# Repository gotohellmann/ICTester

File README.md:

# ICTester

IC Tester for the classic CMOS and TLL ICs with Touch Display

**Beware 5V ICs only!**

GPL v3 License - Open Hard- and Software

Code by  **Frank Hellmann**, 2019
http://www.gotohellmann.com/

based on **Akshay Bawejas** code
http://www.akshaybaweja.com/
https://github.com/akshaybaweja/Smart-IC-Tester

If you like it please leave a ⭐!

For hardware requirements and libraries used see below

### Versions:

**Version 2.6**
----------------------------------------------
- update: updated chipdb.txt with 150+ new ICs
          and checked in new test vectors
- new:    version string for chipdb.txt
- new:    Z tag in chipdb.txt for high-Z check
          needs PCB rework for 1M pull-downs,
          checks not implemented in Version 2.6
- new:    NOVECTORS tag for ICs without tests
          this will only display the IC in manual
- bugfix: Auto: sometimes displays wrong IC pinout    
- update: new CLK code for multiple clockpins
          (thanks, @Hans Hübner)
- new:    Auto: flip result pages back and fore

**Version 2.5**
----------------------------------------------
- new:    added LED support to code
- bugfix: pin order corrected for 20pin ICs
- update: updated chipdb.txt with new ICs
- overall "refactoring" of code ;)

 ### Platform & Hardware needed:
 
- This project needs the [Arduino IDE 1.8.10+](https://www.arduino.cc/en/software)
- a **Arduino Mega 2560** Module
- an **ILI9341** 240x320 Pixel RGB TFT LCD Touch Display Shield
- a 4GB Micro-SD Card that fits the Display Shield 
- the IC Tester PCB with:
   - a 20pin ZIF Socket
   - single row pinheaders (1x6pin, 1x8pin, and two 2x18pin)
   - optional Red/Green-LED (Common Cathode) plus two 220Ohm resistors
   - optional White LED plus one 220Ohm resistors and some heatshrink tubing

### Populating the PCB

- Place the PCB with the soldermask upwards and the ZIF socket left hand side
- First solder the ZIF socket with the lever downwards, as the silkscreen shows
- Optional Good/Fail LED:
    - Solder the Red/Green LED with the Red LED towards the left side
    - Solder in the two 220Ohm resistors R2 and R3
- Optional Worklight LED:
    - Solder in the 220Ohm resistor R1 
    - Keep the long legs of the LED and use some heatshrink to avoid shorts
    - Solder the white LED in and position it
- Solder in the pinheaders
- Plug TFT and PCB into the Arduino Mega 2560

### Setting Up and Programming

- Format the SDCard as FAT/FAT32 Filesystem
- Copy the database (data/chipdb.txt) into the root folder of the SDCard (chipdb.txt)
- Plug the SDCard into the TFT shield and connect the Arduino Mega to the computer  
- Start the Arduino IDE
- Check you have the following librarys installed (Tools -> Library Manager):
  - **MCUFRIEND_kbv**  (try the **Adafruit_ILI9341** if the display doesn't work)
  - **Adafruit GFX Library**  (included the Bus Library as well)
  - **Adafruit Touchscreen**
- Install the _patched_ SD library from this repository (Sketch -> Library -> .ZIP )
  - **SD_patched** (download from above, includes Arduino Mega Software SPI fix)
- Open the **IC_Tester_v2.6.ino** 
- Select the proper **Arduino Mega 2560** under Tools -> Board -> Arduino AVR Boards
- Select the correct COM port for upload
- Compile and Upload the sketch

### Usage

  **Beware: This Tester is for testing 5V ICs only!**

- Start the IC Tester and marvel at the startup screen 😏 
- Touch to enter main screen
- Make sure the ZIF socket lever is up
- Insert IC as shown on the screen with the notch facing up and pull the lever down

**There are two modes of operation:**
- **Auto** tries to detect what kind of IC is inserted. This is helpful if you have no
  markings on the IC. To use it you'll have to adjust the number of pins of the IC
  with the **Pins** Button and then hit **Auto**. The IC Tester will match it against
  the known ICs and give you the results. You can press the touch screen to go through
  each found match.

- **Manual** will check an inserted IC against the tests stored in the database.
  Hit **Manual** and insert the plain IC number without the family code here
  (an 74HC06 should be entered as *7406*) and hit **OK**. This will run the test and
  display the results. You can savely change the IC and retest again, if you have a
  few of the same type to test.
  
  The manual mode can also be used to get the pinout of an IC. Just leave the socket empty.

### Troubleshooting

- Display doesn't work:
  Most of the TFT Touch Display shields work with parallel inputs, that's the reason to use
  the MCUFRIEND_kbv library. If your display does not work, using the original Adafruit_ILI9341
  library could help.

- SD Card Error:
  The chipdb.txt couldn't be read. Either the file is corrupt (copy it again),  the card formated
  with the wrong filesystem (format it with FAT), the card to big (best 4GB or below) or an older SPI 
  library interfers with the the TFT Touch Display shield. If this is the case, install the SD_patched Library
  from this repository above.

### Help needed!

- I do not have all possible TTL 74** or CMOS 4*** ICs here for testing. So if you'll find one, that shows up
  as "*** not found" consider sending it in or add it to the chipdb.txt and test it. The format is pretty
  straight forward.

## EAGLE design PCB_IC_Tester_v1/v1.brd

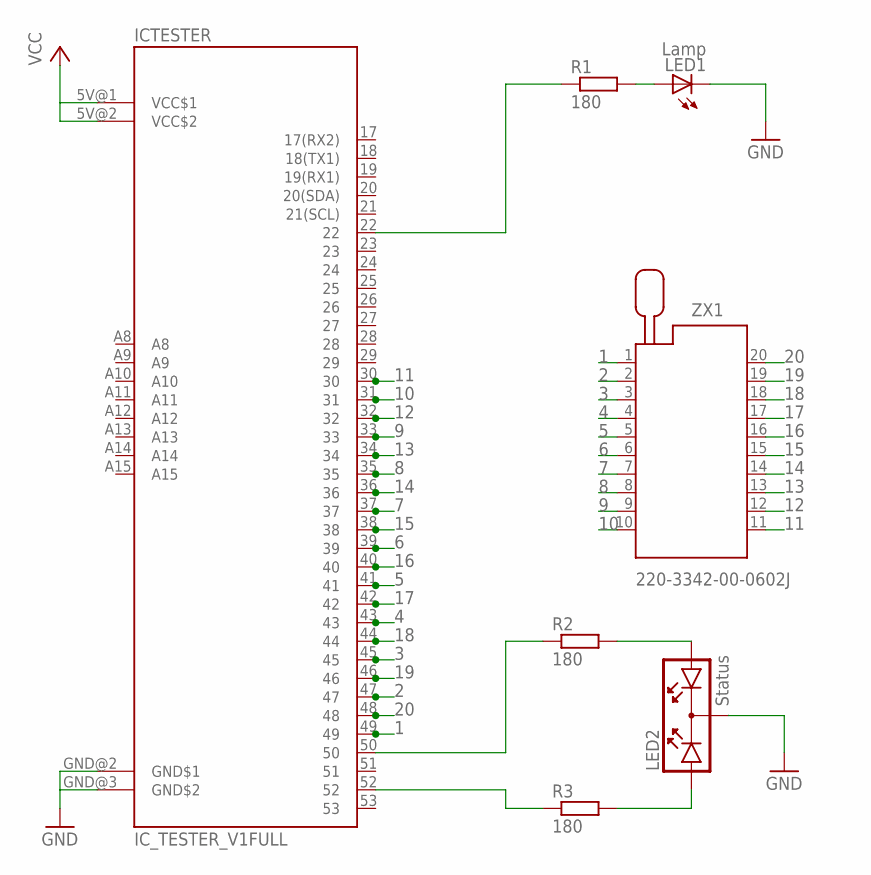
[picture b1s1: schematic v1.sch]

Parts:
ICTESTER: IC_TESTER_V1FULL; SPARKFUN-BOARDS_ARDUINO_MEGA
LED1: Lamp; LED3MM
LED2: Status; DUOLED
R1, R2, R3: 180; 0204V
ZX1: 220-3342-00-0602J

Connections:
1: ICTESTER.49, ZX1.1
2: ICTESTER.47, ZX1.2
3: ICTESTER.45, ZX1.3
4: ICTESTER.43, ZX1.4
5: ICTESTER.41, ZX1.5
6: ICTESTER.39, ZX1.6
7: ICTESTER.37, ZX1.7
8: ICTESTER.35, ZX1.8
9: ICTESTER.33, ZX1.9
10: ICTESTER.31, ZX1.10
11: ICTESTER.30, ZX1.11
12: ICTESTER.32, ZX1.12
13: ICTESTER.34, ZX1.13
14: ICTESTER.36, ZX1.14
15: ICTESTER.38, ZX1.15
16: ICTESTER.40, ZX1.16
17: ICTESTER.42, ZX1.17
18: ICTESTER.44, ZX1.18
19: ICTESTER.46, ZX1.19
20: ICTESTER.48, ZX1.20
GND: ICTESTER.GND@2 (GND$1), ICTESTER.GND@3 (GND$2), LED1.K (C), LED2.K
unnamed: LED1.A, R1.2
unnamed: LED2.A2, R2.2
unnamed: LED2.A1, R3.2
unnamed: ICTESTER.50, R2.1
unnamed: ICTESTER.52, R3.1
unnamed: ICTESTER.22, R1.1
VCC: ICTESTER.5V@1 (VCC$1), ICTESTER.5V@2 (VCC$2)

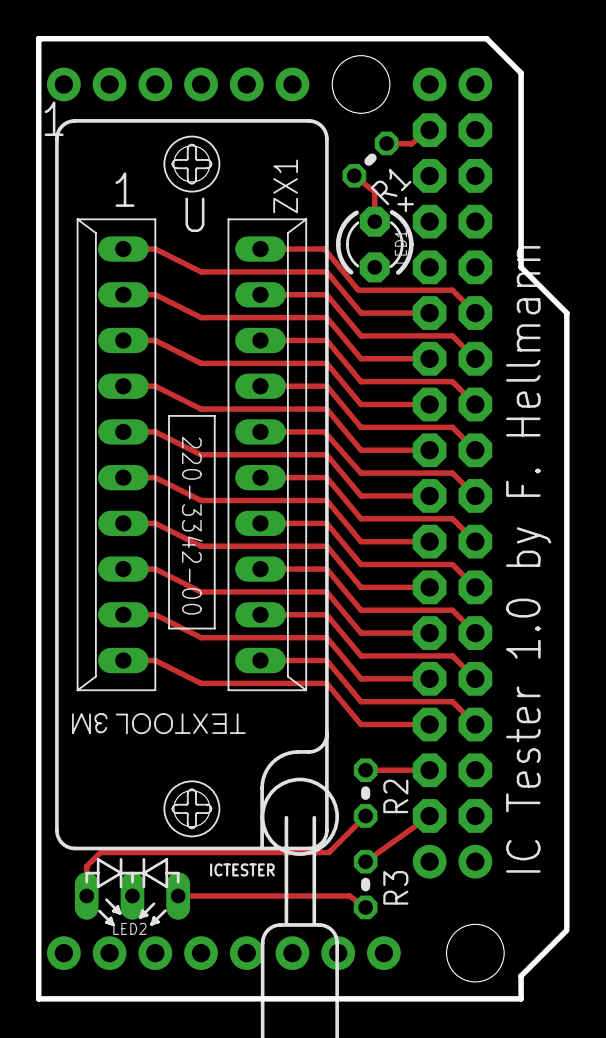
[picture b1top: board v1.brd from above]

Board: 2 copper layers, 29.3 x 53.3 mm, 7 parts (0 on the bottom side), 28 nets.

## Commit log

2021-01-27 Initial commit
    Arduino codebase and database commited
2021-01-27 Initial Commit
    Eagle Project and Gerbers
2021-01-31 Update IC_Tester_v2.5.ino
    include SD_patched.h with Arduino Mega 2560 Software SPI patches
2021-01-31 Patched SD.h Library
    This library contains a patched SD.h library to access SD Cards with Software SPI on an Arduino Mega 2560
